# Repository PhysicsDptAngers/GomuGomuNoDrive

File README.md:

# Rubber Zener (GomuGomuNoDrive): Analog Circuit & Anti-Aliased Virtual Analog Model

This repository provides open-source hardware designs, physical bench measurement datasets, numerical simulation routines, and real-time DSP emulations for the **Rubber Zener** clipping topology.

The Rubber Zener is a parameterized audio clipping circuit based on the bipolar junction transistor (BJT) $V_{be}$ multiplier, augmented with local passive and reactive networks. It allows decoupled analog tuning of positive and negative conduction thresholds, soft-knee transition slopes, deep-saturation current ceilings, frequency-dependent clipping profiles, and envelope-dependent DC baseline sag.

> **Academic Context:**  
> This repository contains the reference implementation, experimental datasets, and validation routines accompanying the research paper:  
> *The Rubber Zener Clipping Topology: Circuit Analysis, Dynamic Characterization, and Anti-Aliased Virtual Analog Modeling* (currently under peer review).

---

## コムコム の Drive  (Gomu Gomu No Drive) ?

The $V_{be}$ multiplier circuit is sometimes called "Rubber Zener" because, like rubber, its threshold is malleable. In pop culture, the most well-known "rubber man" is *Luffy* (ルフィ) from *One Piece* (ワンピース). His iconic attack names start with "ゴムゴム" (Gomu Gomu) since ゴム (gomu) in Japanese means rubber. Hence the name of this distortion pedal: コムコム の Drive (Gomu Gomu No Drive).

---

## Repository Structure

```text
GomuGomuNoDrive/
├── Data/
│   ├── AC/                                # AC bench measurements, steady-state datasets, and fitting scripts
│   └── DC characteristics/                # Static I-V measurement datasets
├── Hardware/
│   ├── GomuGomuNoDrive_hard/              # Shunt dipole hard-clipping implementation (KiCad, 3D models, Gerbers)
│   └── GomuGomuNoDrive_Soft/              # Feedback loop soft-clipping implementation (KiCad, BOM, production files)
├── NumericalSimulation/                   # SPICE benchmarks, 4D ODE solvers, harmonic balance, and validation routines
└── Software/
    ├── Faust/                             # Faust core DSP architecture and C++ wrappers
    ├── JesuSonic/                         # Real-time JSFX implementation for Cockos REAPER
    └── Juce Plugin/                       # Full C++ audio plugin project (VST3, CLAP, LV2, Standalone)
```

#### Pre-compiled Binaries

Pre-compiled binaries for 64-bit Windows and Linux systems (VST3 and Standalone) are provided under the [Releases](../../releases) section.

---

## License

This project adopts a multi-licensing scheme adapted to its different components:

- **Software** (JUCE audio plugin, DSP solvers, simulation scripts): Licensed under the [GNU General Public License v3.0](LICENSE-GPL.txt) (GPL-3.0-or-later). Bundled cabinet impulse responses are licensed under GPL-2.0-or-later (Copyright © 2013 David Fau Casquel / Guitarix project).
- **Hardware** (KiCad schematics, PCB layouts, manufacturing files): Licensed under the [CERN Open Hardware Licence Version 2 – Strongly Reciprocal](LICENSE-CERN.txt) (CERN-OHL-S-2.0).
- **Documentation & Data** (Manuscript, figures, measurement datasets): Licensed under the [Creative Commons Attribution 4.0 International License](https://creativecommons.org/licenses/by/4.0/) (CC-BY-4.0).

---

## Citation

If you use this circuit topology, DSP implementation, or dataset in academic work or derivative projects, please cite:

TBA !

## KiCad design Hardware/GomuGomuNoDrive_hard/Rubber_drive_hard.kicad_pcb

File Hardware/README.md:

# Hardware

Contains complete CAD files, schematics, PCB layouts, and fabrication packages:

* **`GomuGomuNoDrive_hard`**: The primary shunt-to-ground clipping dipole topology characterized in the paper.
* **`GomuGomuNoDrive_Soft`**: Alternative operational amplifier feedback implementation (compatible with classic LM308 / dual op-amp footprints).

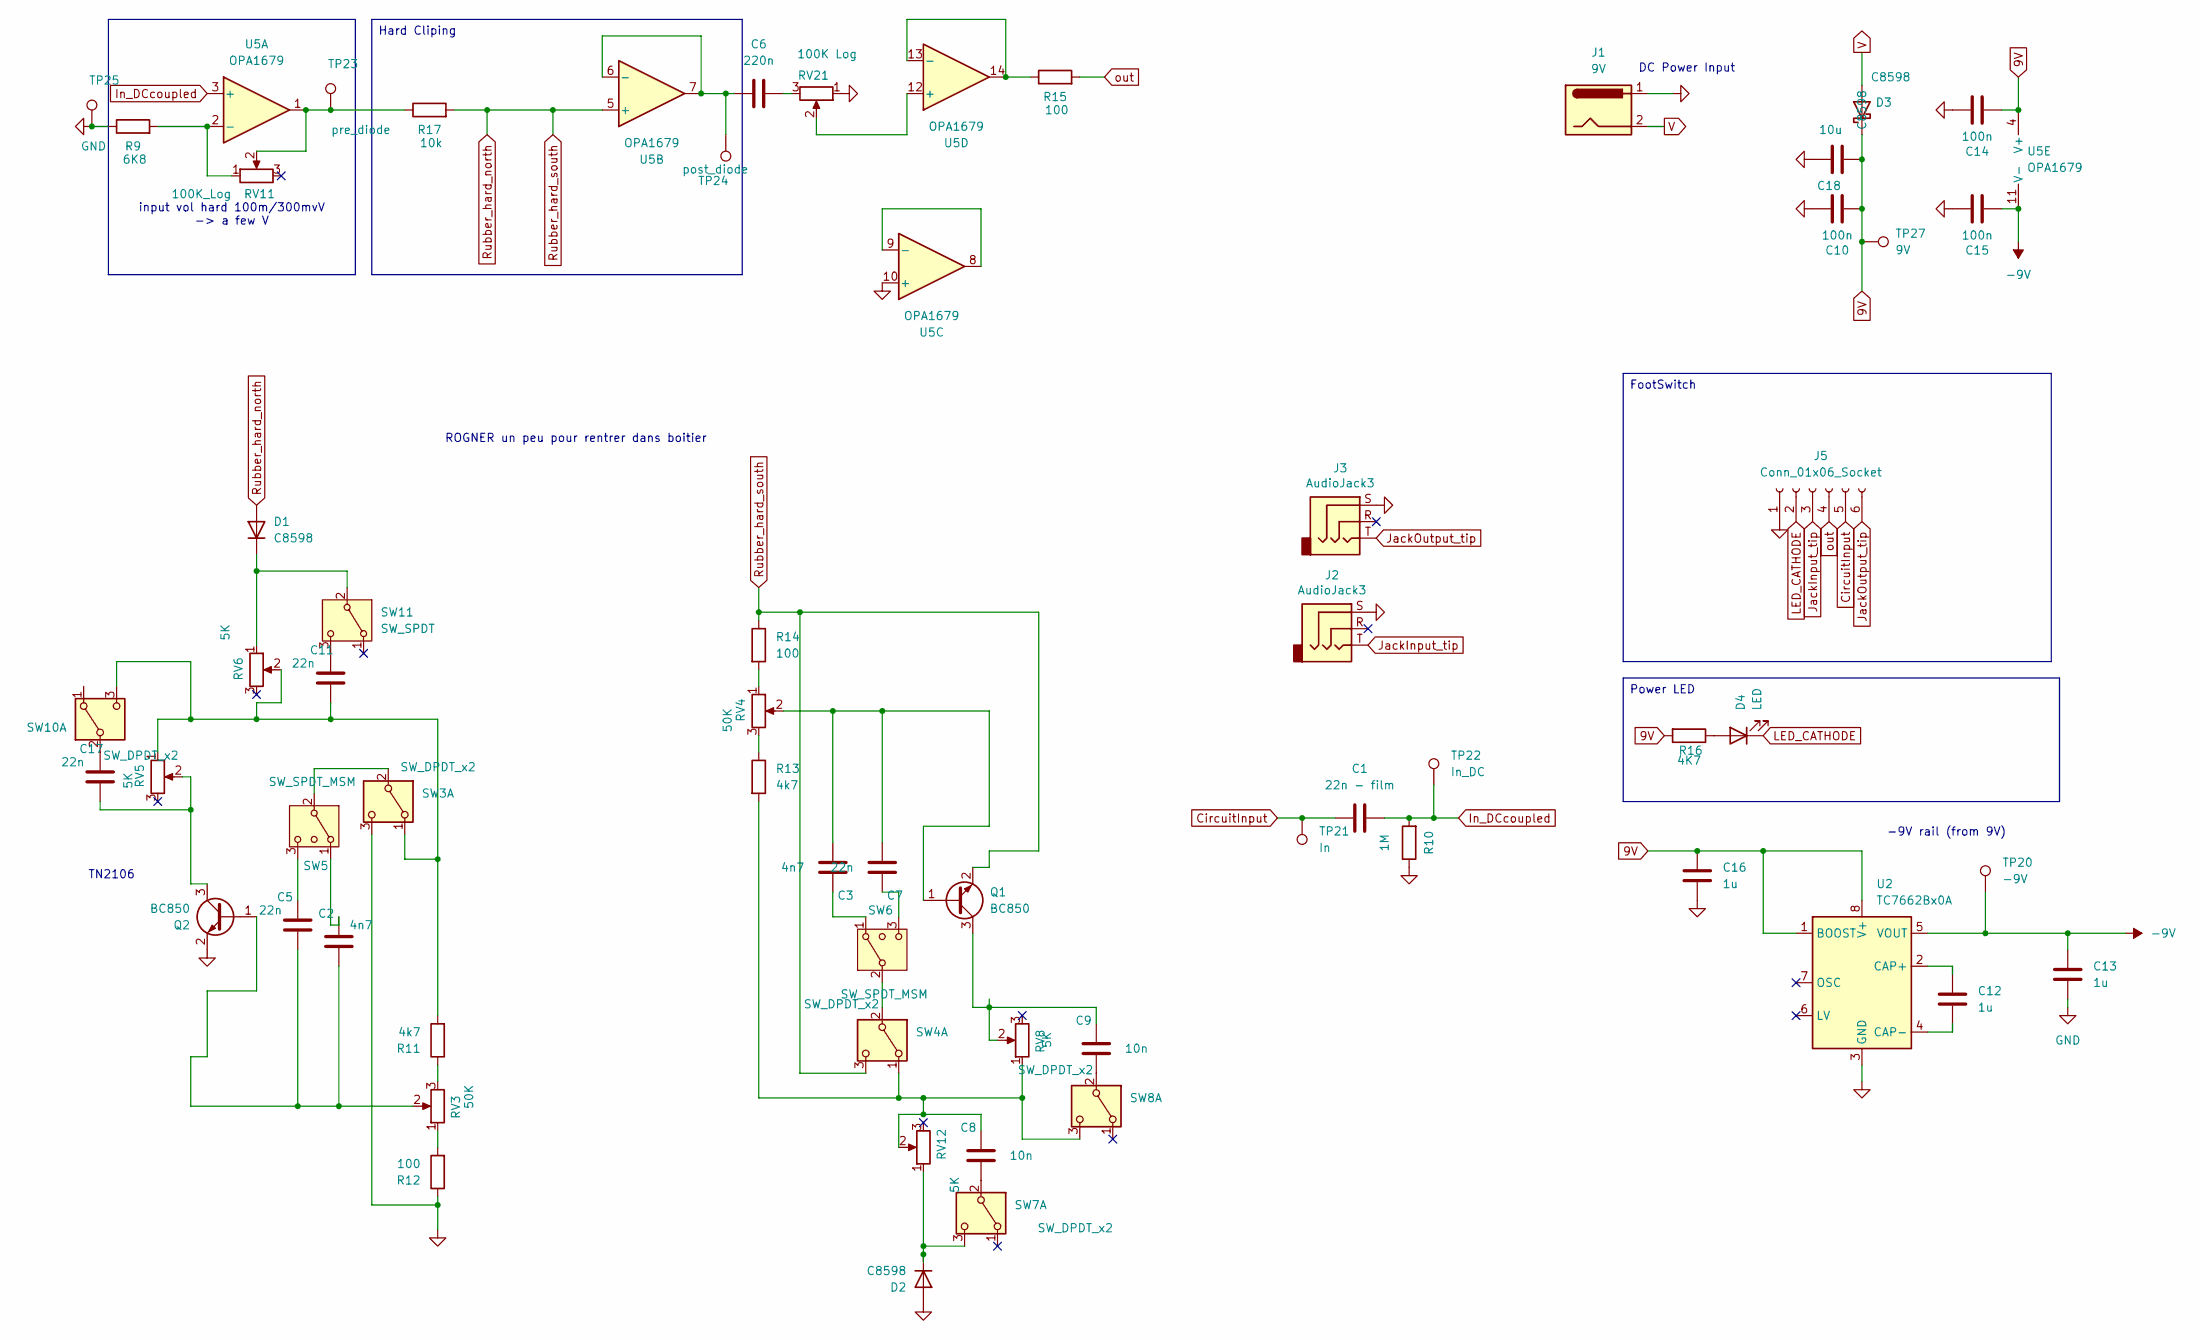
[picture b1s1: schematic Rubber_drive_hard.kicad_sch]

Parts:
C1: 22n - film; C_0805_2012Metric_Pad1.18x1.45mm_HandSolder
C2, C3: 4n7; C_0805_2012Metric_Pad1.18x1.45mm_HandSolder
C5, C7, C11, C17: 22n; C_0805_2012Metric_Pad1.18x1.45mm_HandSolder
C6: 220n; C_0805_2012Metric_Pad1.18x1.45mm_HandSolder
C8, C9: 10n; C_0805_2012Metric_Pad1.18x1.45mm_HandSolder
C10, C14, C15: 100n; C_0805_2012Metric_Pad1.18x1.45mm_HandSolder
C12, C13, C16: 1u; C_0805_2012Metric_Pad1.18x1.45mm_HandSolder
C18: 10u; C_0805_2012Metric_Pad1.18x1.45mm_HandSolder
D1, D2, D3: C8598; D_SOD-123
D4: LED; LED_D5.0mm_Clear
J1: 9V; BarrelJack_Horizontal
J2, J3: AudioJack3; Jack_6.35mm_Neutrik_NMJ6HCD2_Horizontal
J5: Conn_01x06_Socket; JST_EH_B6B-EH-A_1x06_P2.50mm_Vertical
Q1, Q2: BC850; SOT-23
R9: 6K8; R_0805_2012Metric_Pad1.20x1.40mm_HandSolder
R10: 1M; R_0805_2012Metric_Pad1.20x1.40mm_HandSolder
R11, R13: 4k7; R_0805_2012Metric_Pad1.20x1.40mm_HandSolder
R12, R14, R15: 100; R_0805_2012Metric_Pad1.20x1.40mm_HandSolder
R16: 4K7; R_0805_2012Metric_Pad1.20x1.40mm_HandSolder
R17: 10k; R_0805_2012Metric_Pad1.20x1.40mm_HandSolder
RV3, RV4: 50K; Potentiometer_Alpha_RD901F-40-00D_Single_Vertical
RV5, RV6, RV8, RV12: 5K; Potentiometer_Alpha_RD901F-40-00D_Single_Vertical
RV11: 100K_Log; Potentiometer_Alpha_RD901F-40-00D_Single_Vertical
RV21: 100K Log; Potentiometer_Alpha_RD901F-40-00D_Single_Vertical
SW3, SW4: SW_DPDT_x2; SW_MINI-SPDT-SW
SW5, SW6: SW_SPDT_MSM; SW_MINI-SPDT-SW
SW7, SW8, SW10: SW_DPDT_x2; SS12D00
SW11: SW_SPDT; SS12D00
TP20: -9V; PinHeader_1x01_P2.54mm_Vertical
TP21: In; PinHeader_1x01_P2.54mm_Vertical
TP22: In_DC; PinHeader_1x01_P2.54mm_Vertical
TP23: pre_diode; PinHeader_1x01_P2.54mm_Vertical
TP24: post_diode; PinHeader_1x01_P2.54mm_Vertical
TP25: GND; PinHeader_1x01_P2.54mm_Vertical
TP27: 9V; PinHeader_1x01_P2.54mm_Vertical
U2: TC7662Bx0A; SOIC-8_3.9x4.9mm_P1.27mm
U5: OPA1679; SOIC-14_3.9x8.7mm_P1.27mm

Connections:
9V: C10.2, C14.2, C16.2, C18.2, D3.1 (K), R16.2, TP27.1 (1_1), U2.1 (BOOST), U2.8 (V+), U5.4 (V+)
-9V: C13.2, C15.2, TP20.1 (1_1), U2.5 (VOUT), U5.11 (V-)
CircuitInput: C1.1, J5.5, TP21.1 (1_1)
GND: C10.1, C13.1, C14.1, C15.1, C16.1, C18.1, D2.2 (A), J1.1, J2.S, J3.S, J5.1, Q2.2 (E), R9.1, R10.1, R12.1, RV21.1, SW3.3 (C), TP25.1 (1_1), U2.3 (GND), U5.10 (+)
In_DCcoupled: C1.2, R10.2, TP22.1 (1_1), U5.3 (+)
JackInput_tip: J2.T, J5.3
JackOutput_tip: J3.T, J5.6
LED_CATHODE: D4.1 (K), J5.2
unnamed: C2.1, SW5.1
unnamed: C3.1, SW6.1
unnamed: C6.2, RV21.3
unnamed: D1.1 (K), RV6.1, SW11.2 (B)
unnamed: D2.1 (K), RV12.1, SW7.3 (C)
unnamed: D4.2 (A), R16.1
unnamed: C3.2, C7.2, Q1.1 (B), RV4.2
unnamed: C9.1, Q1.3 (C), RV8.2
unnamed: C2.2, C5.2, Q2.1 (B), RV3.2
unnamed: C17.2, Q2.3 (C), RV5.2
unnamed: R11.1, RV3.3
unnamed: R12.2, RV3.1
unnamed: R13.1, RV4.3
unnamed: R14.2, RV4.1
unnamed: R17.1, RV11.2, TP23.1 (1_1), U5.1
unnamed: SW3.2 (B), SW5.2 (3)
unnamed: C8.1, R13.2, RV8.1, RV12.2, SW4.1 (A), SW8.3 (C)
unnamed: SW4.2 (B), SW6.2 (3)
unnamed: C5.1, SW5.3 (4)
unnamed: C7.1, SW6.3 (4)
unnamed: C8.2, SW7.2 (B)
unnamed: C9.2, SW8.2 (B)
unnamed: C17.1, SW10.2 (B)
unnamed: C11.2, R11.2, RV5.1, RV6.2, SW3.1 (A), SW10.3 (C)
unnamed: C11.1, SW11.3 (C)
unnamed: C12.2, U2.2 (CAP+)
unnamed: C12.1, U2.4 (CAP-)
unnamed: R9.2, RV11.1, U5.2 (-)
unnamed: C6.1, TP24.1 (1_1), U5.6 (-), U5.7
unnamed: U5.8, U5.9 (-)
unnamed: RV21.2, U5.12 (+)
unnamed: R15.1, U5.13 (-), U5.14
Rubber_hard_north: D1.2 (A), Q1.2 (E), R14.1, R17.2, SW4.3 (C), U5.5 (+)
V: D3.2 (A), J1.2
out: J5.4, R15.2; also elsewhere on the board

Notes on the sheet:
input vol hard 100m/300mvV -> a few V
TN2106
-9V rail (from 9V)
ROGNER un peu pour rentrer dans boitier
DC Power Input
FootSwitch
Hard Cliping
Power LED

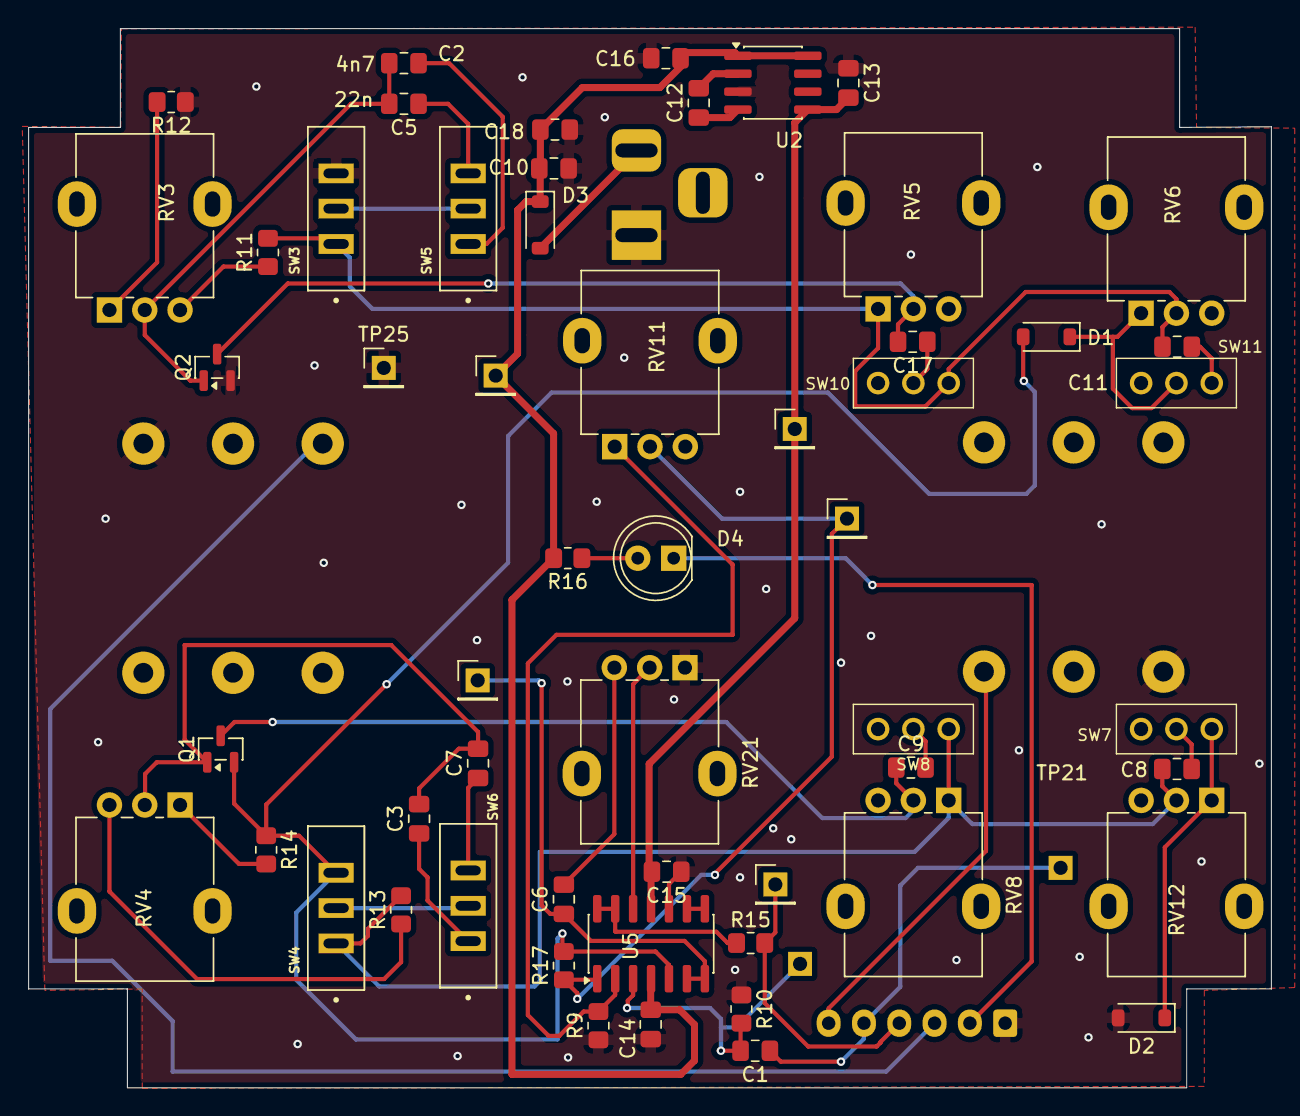
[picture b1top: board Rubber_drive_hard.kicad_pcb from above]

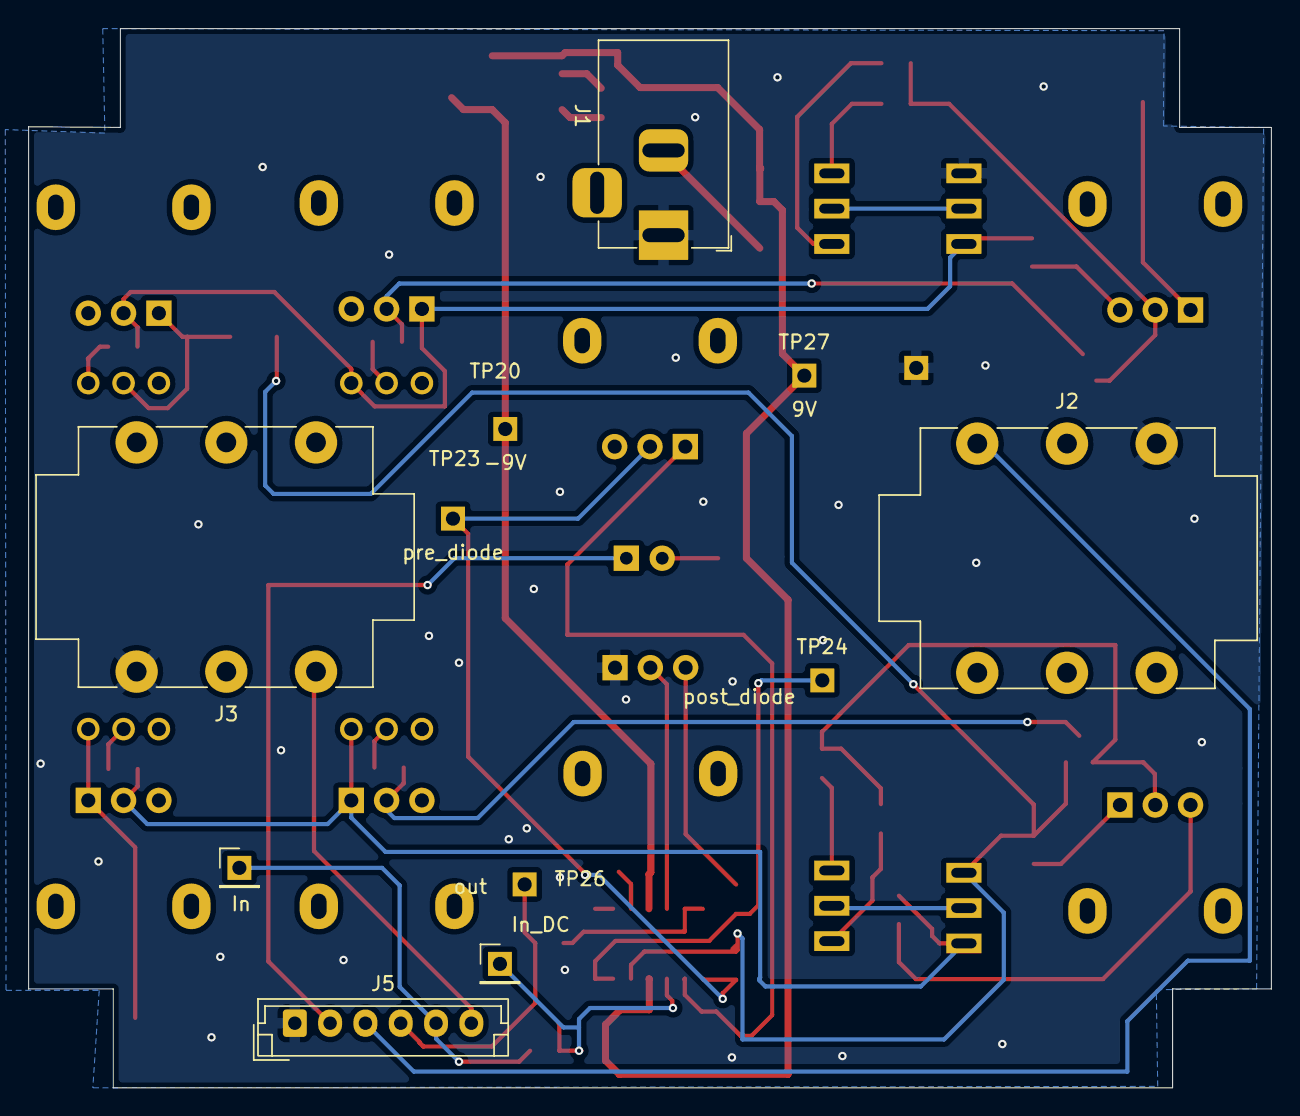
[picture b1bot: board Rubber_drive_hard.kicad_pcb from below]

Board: 2 copper layers, 88.0 x 75.0 mm, 62 parts (6 on the bottom side), 43 nets.

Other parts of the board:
TP26: out; PinHeader_1x01_P2.54mm_Vertical

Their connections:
out: TP26.1 (1_1); also elsewhere on the board

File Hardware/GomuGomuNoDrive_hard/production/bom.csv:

Designator,Footprint,Quantity,Value,LCSC Part #
C1,0805,1,22n - film,
"C10, C14, C15",0805,3,100n,
"C11, C17, C5, C7",0805,4,22n,
"C12, C13, C16",0805,3,1u,
C18,0805,1,10u,
"C2, C3",0805,2,4n7,
C6,0805,1,220n,
"C8, C9",0805,2,10n,
"D1, D2, D3",D_SOD-123,3,C8598,
D4,LED_D5.0mm_Clear,1,LED,
J1,BarrelJack_Horizontal,1,9V,
"J2, J3",Jack_6.35mm_Neutrik_NMJ6HCD2_Horizontal,2,AudioJack3,
J5,JST_EH_B6B-EH-A_1x06_P2.50mm_Vertical,1,Conn_01x06_Socket,
"Q1, Q2",SOT-23,2,BC850,
R10,0805,1,1M,
"R11, R13, R16",0805,3,4k7,
"R12, R14, R15",0805,3,100,
R17,0805,1,10k,
R9,0805,1,6K8,
RV11,Potentiometer_Alpha_RD901F-40-00D_Single_Vertical,1,100K_Log,
"RV12, RV5, RV6, RV8",Potentiometer_Alpha_RD901F-40-00D_Single_Vertical,4,5K,
RV21,Potentiometer_Alpha_RD901F-40-00D_Single_Vertical,1,100K Log,
"RV3, RV4",Potentiometer_Alpha_RD901F-40-00D_Single_Vertical,2,50K,
"SW10, SW7, SW8",SS12D00,3,SW_DPDT_x2,
SW11,SS12D00,1,SW_SPDT,
"SW3, SW4",SW_MINI-SPDT-SW,2,SW_DPDT_x2,
"SW5, SW6",SW_MINI-SPDT-SW,2,SW_SPDT_MSM,
TP20,PinHeader_1x01_P2.54mm_Vertical,1,-9V,
TP21,PinHeader_1x01_P2.54mm_Vertical,1,In,
TP22,PinHeader_1x01_P2.54mm_Vertical,1,In_DC,
TP23,PinHeader_1x01_P2.54mm_Vertical,1,pre_diode,
TP24,PinHeader_1x01_P2.54mm_Vertical,1,post_diode,
TP25,PinHeader_1x01_P2.54mm_Vertical,1,GND,
TP26,PinHeader_1x01_P2.54mm_Vertical,1,out,
TP27,PinHeader_1x01_P2.54mm_Vertical,1,9V,
U2,SOIC-8_3.9x4.9mm_P1.27mm,1,TC7662Bx0A,
U5,SOIC-14_3.9x8.7mm_P1.27mm,1,OPA1679,

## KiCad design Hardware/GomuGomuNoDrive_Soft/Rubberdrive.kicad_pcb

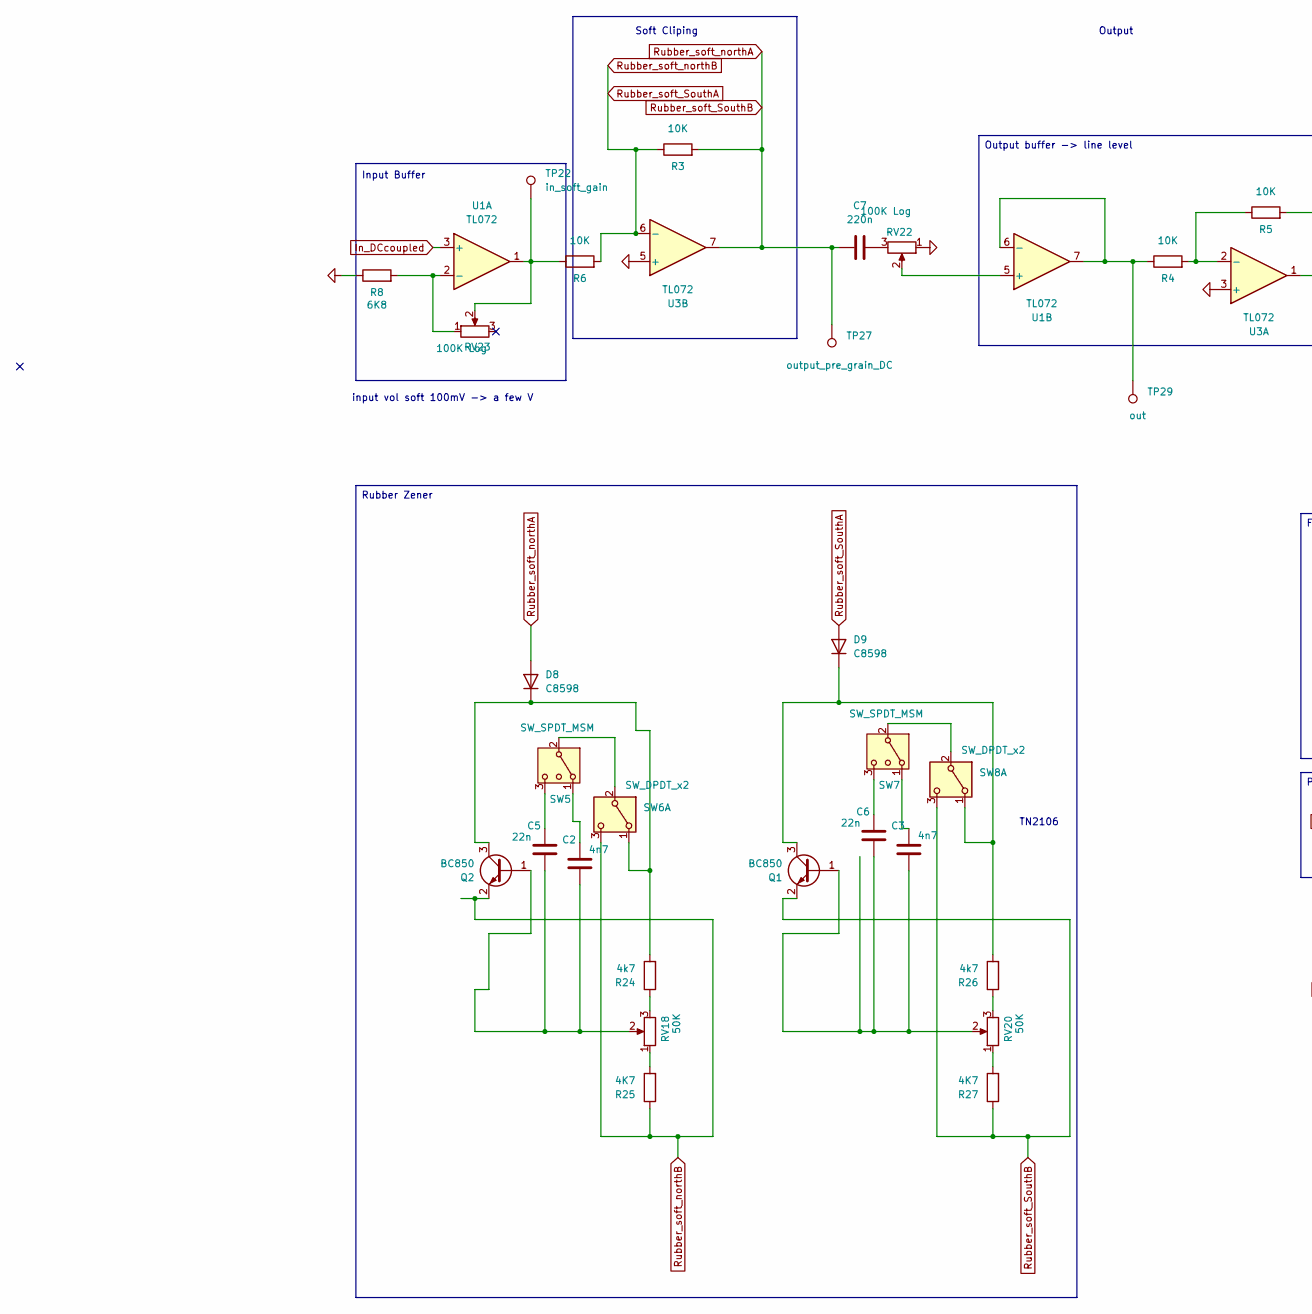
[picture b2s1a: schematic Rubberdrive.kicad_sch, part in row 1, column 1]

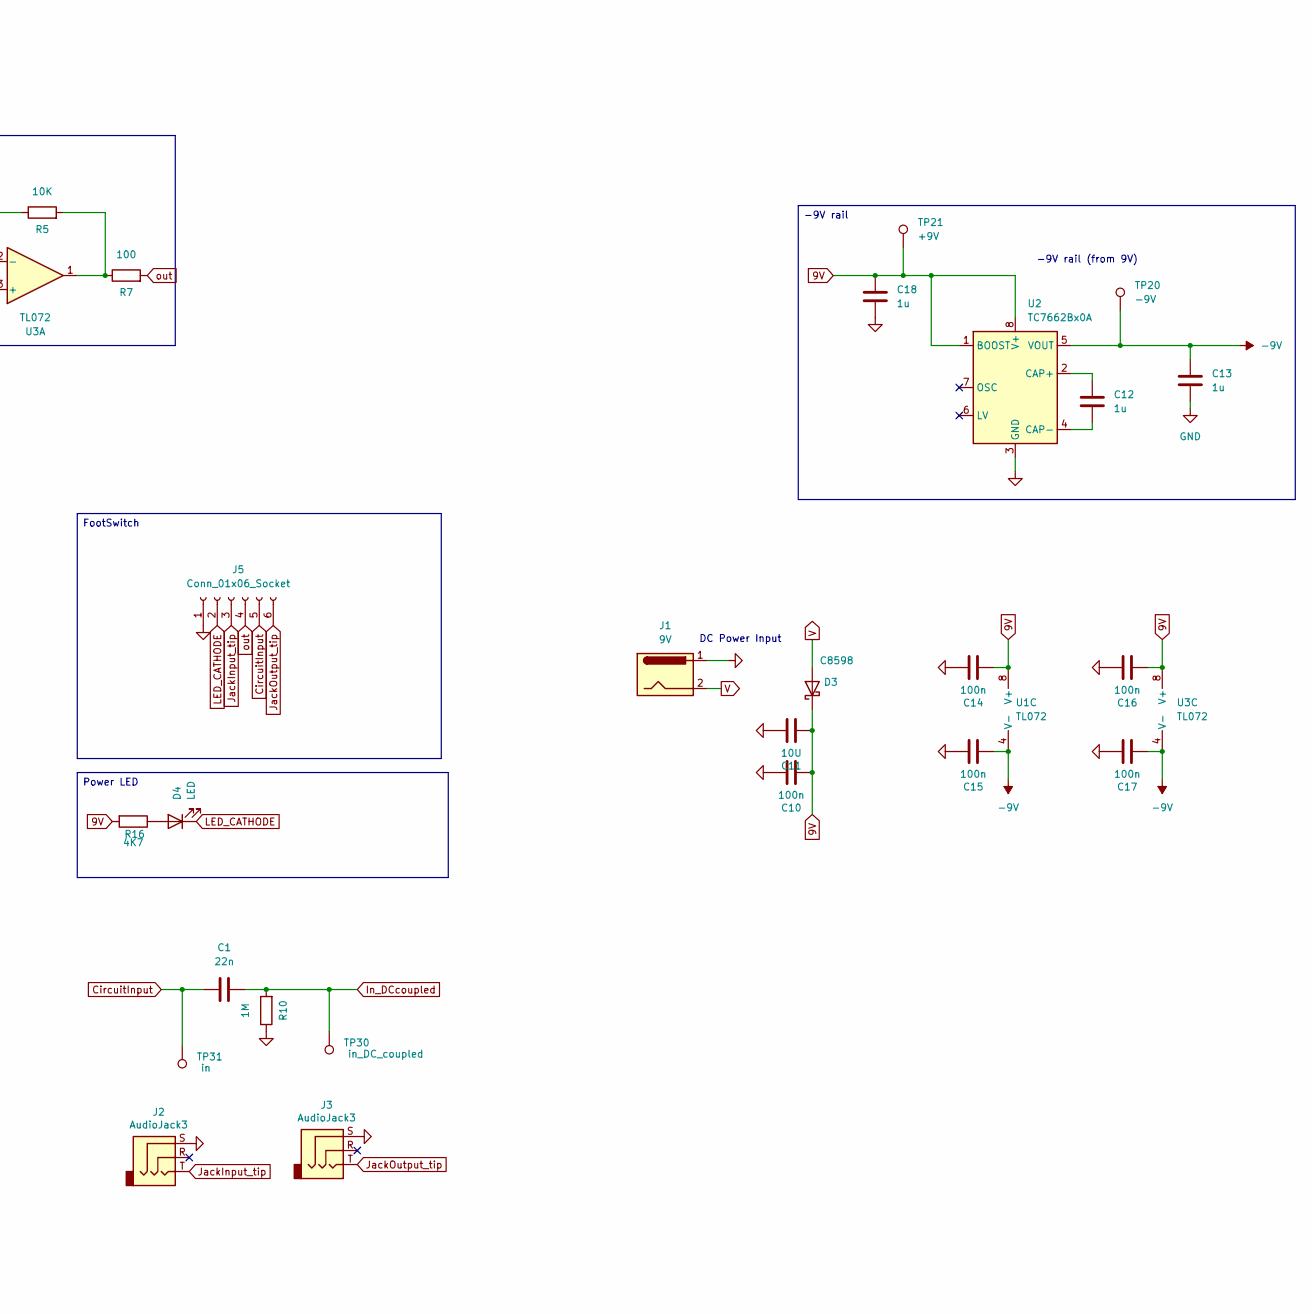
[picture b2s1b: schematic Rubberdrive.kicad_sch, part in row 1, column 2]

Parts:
C1, C5, C6: 22n; C_0805_2012Metric_Pad1.18x1.45mm_HandSolder
C2, C3: 4n7; C_0805_2012Metric_Pad1.18x1.45mm_HandSolder
C7: 220n; C_0805_2012Metric_Pad1.18x1.45mm_HandSolder
C10, C14, C15, C16, C17: 100n; C_0805_2012Metric_Pad1.18x1.45mm_HandSolder
C11: 10U; C_1206_3216Metric_Pad1.33x1.80mm_HandSolder
C12, C13, C18: 1u; C_0805_2012Metric_Pad1.18x1.45mm_HandSolder
D3, D8, D9: C8598; D_SOD-123
D4: LED; LED_D5.0mm_Clear
J1: 9V; BarrelJack_Horizontal
J2, J3: AudioJack3; Jack_6.35mm_Neutrik_NMJ6HCD2_Horizontal
J5: Conn_01x06_Socket; JST_EH_B6B-EH-A_1x06_P2.50mm_Vertical
Q1, Q2: BC850; SOT-23
R3, R4, R5, R6: 10K; R_0805_2012Metric_Pad1.20x1.40mm_HandSolder
R7: 100; R_0805_2012Metric_Pad1.20x1.40mm_HandSolder
R8: 6K8; R_0805_2012Metric_Pad1.20x1.40mm_HandSolder
R10: 1M; R_0805_2012Metric_Pad1.20x1.40mm_HandSolder
R16, R25, R27: 4K7; R_0805_2012Metric_Pad1.20x1.40mm_HandSolder
R24, R26: 4k7; R_0805_2012Metric_Pad1.20x1.40mm_HandSolder
RV18, RV20: 50K; Potentiometer_Alpha_RD901F-40-00D_Single_Vertical
RV22, RV23: 100K Log; Potentiometer_Alpha_RD901F-40-00D_Single_Vertical
SW5, SW7: SW_SPDT_MSM; SW_MINI-SPDT-SW
SW6, SW8: SW_DPDT_x2; SW_MINI-SPDT-SW
TP20: -9V; PinHeader_1x01_P2.54mm_Vertical
TP21: +9V; PinHeader_1x01_P2.54mm_Vertical
TP22: in_soft_gain; PinHeader_1x01_P2.54mm_Vertical
TP27: output_pre_grain_DC; PinHeader_1x01_P2.54mm_Vertical
TP29: out; PinHeader_1x01_P2.54mm_Vertical
TP30: in_DC_coupled; PinHeader_1x01_P2.54mm_Vertical
TP31: in; PinHeader_1x01_P2.54mm_Vertical
U1, U3: TL072; DIP-8_W7.62mm
U2: TC7662Bx0A; SOIC-8_3.9x4.9mm_P1.27mm

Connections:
9V: C10.2, C11.2, C14.2, C16.2, C18.2, D3.1 (K), R16.2, TP21.1 (1_1), U1.8 (V+), U2.1 (BOOST), U2.8 (V+), U3.8 (V+)
-9V: C13.2, C15.2, C17.2, TP20.1 (1_1), U1.4 (V-), U2.5 (VOUT), U3.4 (V-)
CircuitInput: C1.1, J5.5, TP31.1 (1_1)
GND: C10.1, C11.1, C13.1, C14.1, C15.1, C16.1, C17.1, C18.1, J1.1, J2.S, J3.S, J5.1, R8.1, R10.1, RV22.1, U2.3 (GND), U3.3 (+), U3.5 (+)
In_DCcoupled: C1.2, R10.2, TP30.1 (1_1), U1.3 (+)
JackInput_tip: J2.T, J5.3
JackOutput_tip: J3.T, J5.6
LED_CATHODE: D4.1 (K), J5.2
unnamed: C2.1, SW5.1
unnamed: C3.1, SW7.1
unnamed: C7.2, RV22.3
unnamed: D4.2 (A), R16.1
unnamed: D8.1 (K), Q2.3 (C), R24.2, SW6.1 (A)
unnamed: D9.1 (K), Q1.3 (C), R26.2, SW8.1 (A)
unnamed: C3.2, C6.2, Q1.1 (B), RV20.2
unnamed: C2.2, C5.2, Q2.1 (B), RV18.2
unnamed: R5.2, R7.1, U3.1
unnamed: R6.1, RV23.2, TP22.1 (1_1), U1.1
unnamed: R24.1, RV18.3
unnamed: R25.2, RV18.1
unnamed: R26.1, RV20.3
unnamed: R27.2, RV20.1
unnamed: SW5.2 (3), SW6.2 (B)
unnamed: C5.1, SW5.3 (4)
unnamed: SW7.2 (3), SW8.2 (B)
unnamed: C6.1, SW7.3 (4)
unnamed: R8.2, RV23.1, U1.2 (-)
unnamed: RV22.2, U1.5 (+)
unnamed: R4.1, TP29.1 (1_1), U1.6 (-), U1.7
unnamed: C12.2, U2.2 (CAP+)
unnamed: C12.1, U2.4 (CAP-)
unnamed: R4.2, R5.1, U3.2 (-)
Rubber_soft_SouthA: D9.2 (A), Q2.2 (E), R3.1, R6.2, R25.1, SW6.3 (C), U3.6 (-)
Rubber_soft_SouthB: C7.1, D8.2 (A), Q1.2 (E), R3.2, R27.1, SW8.3 (C), TP27.1 (1_1), U3.7
V: D3.2 (A), J1.2
out: J5.4, R7.2

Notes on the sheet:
Output
input vol soft 100mV -> a few V
Soft Cliping
TN2106
-9V rail (from 9V)
Input Buffer
DC Power Input
Power LED
Output buffer -> line level
-9V rail
FootSwitch
Rubber Zener

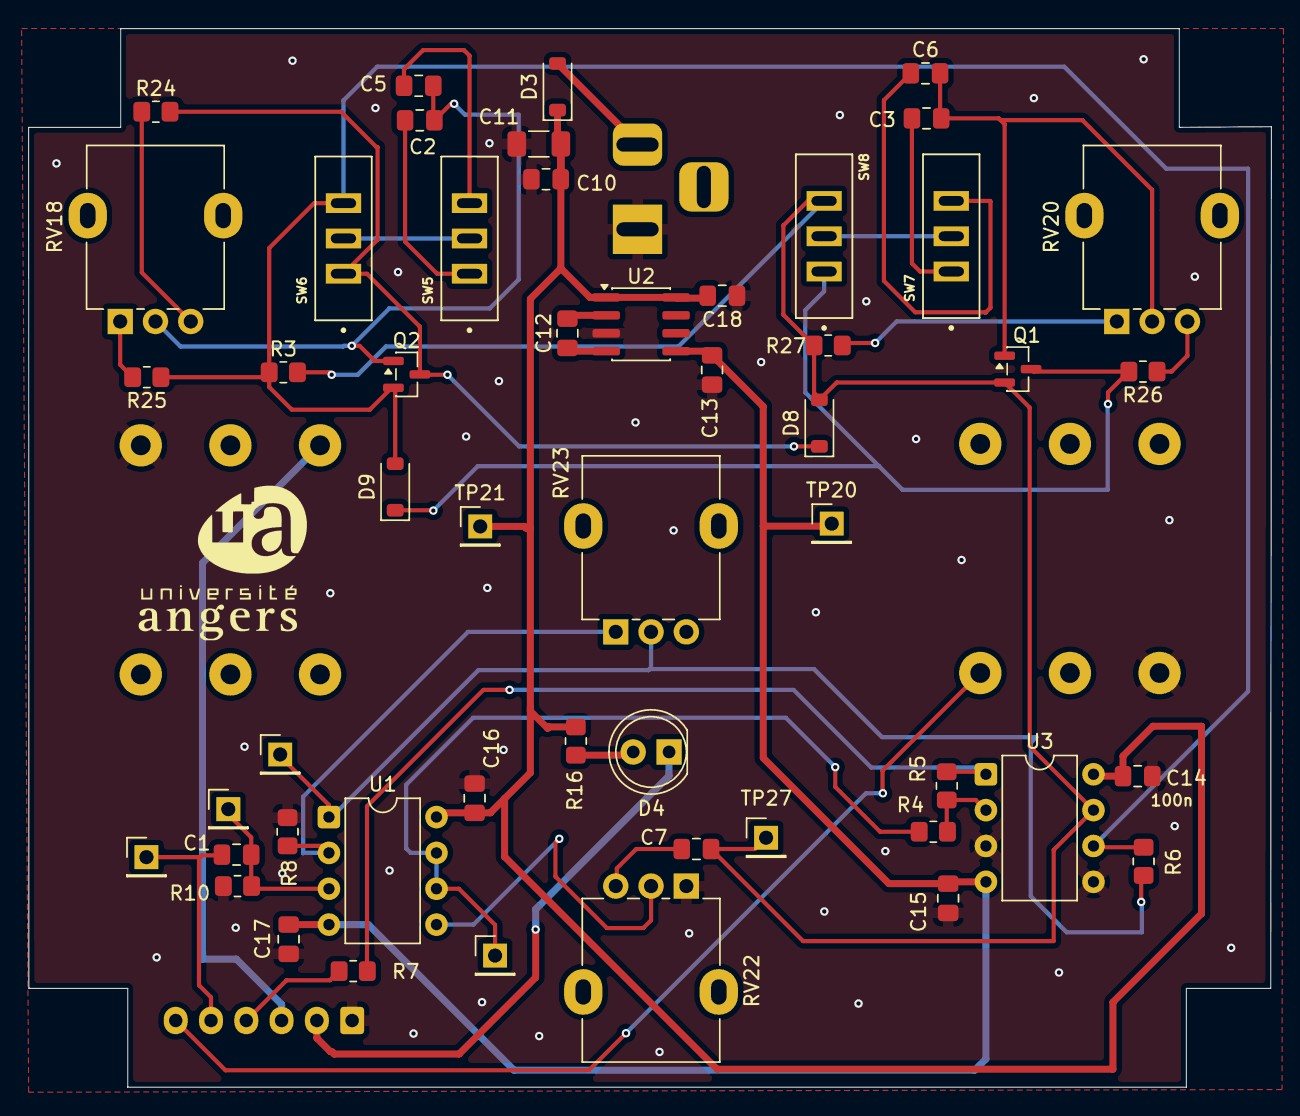
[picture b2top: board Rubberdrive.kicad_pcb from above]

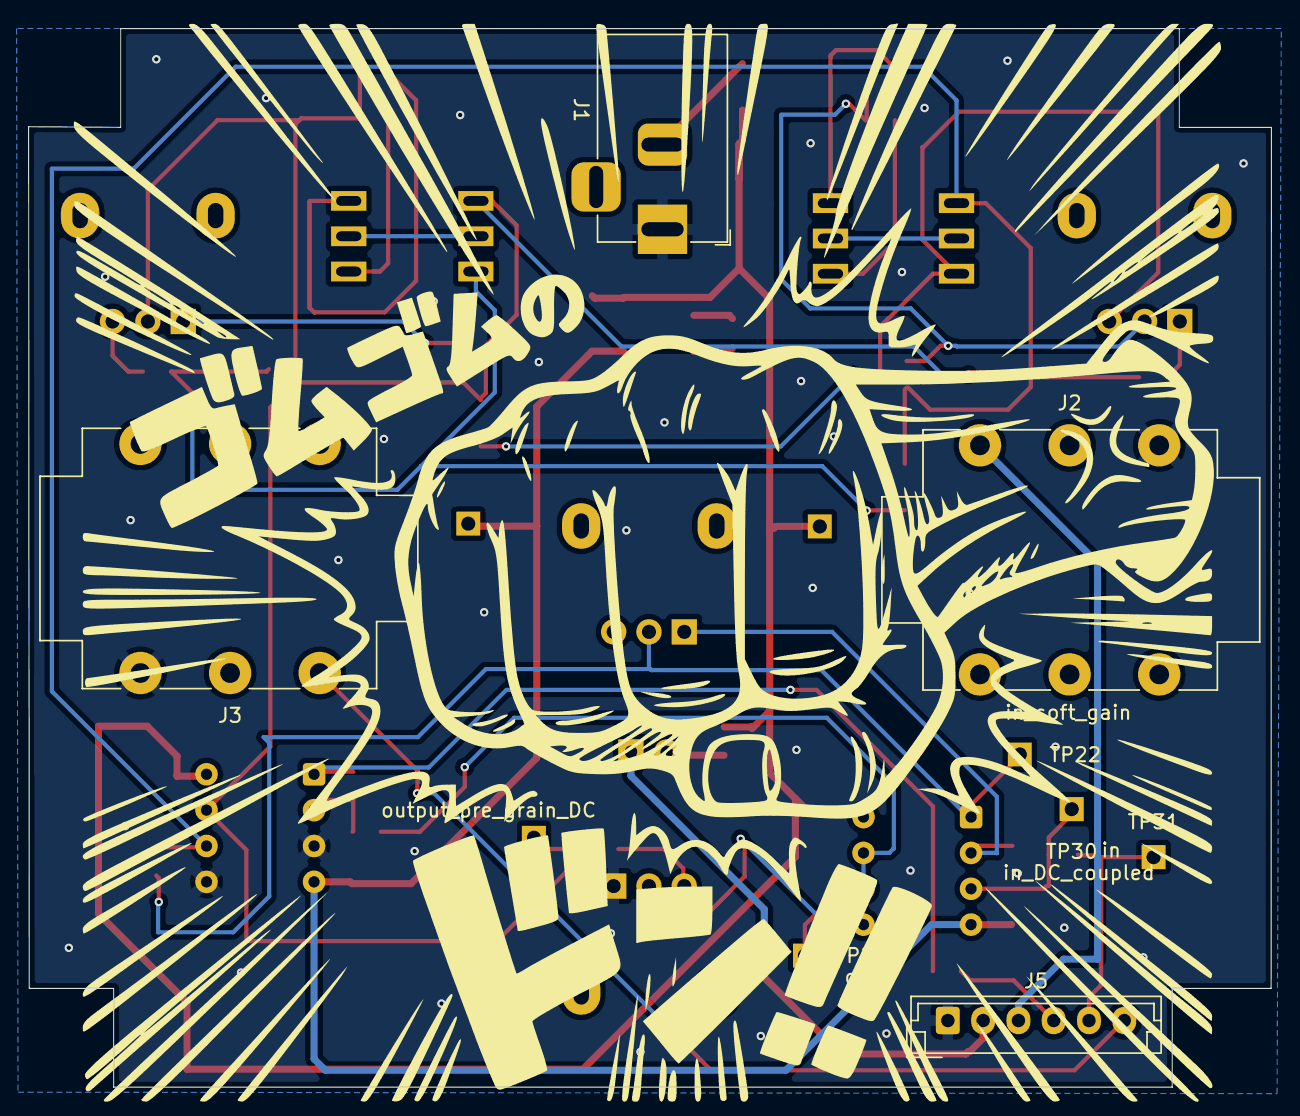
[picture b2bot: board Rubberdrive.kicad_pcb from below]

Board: 2 copper layers, 88.1 x 75.0 mm, 55 parts (4 on the bottom side), 36 nets.
